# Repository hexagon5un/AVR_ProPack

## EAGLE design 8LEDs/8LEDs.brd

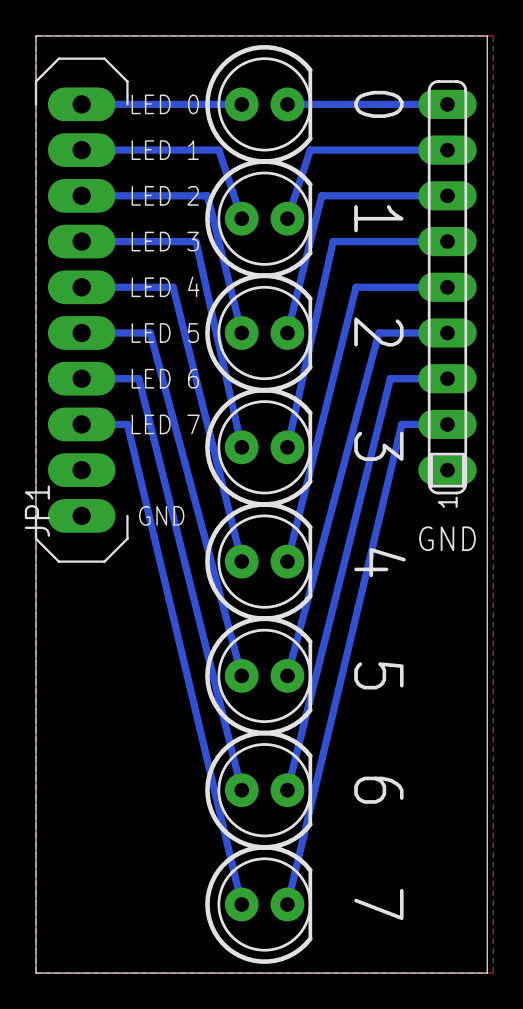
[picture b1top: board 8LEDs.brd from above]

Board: 2 copper layers, 25.1 x 52.1 mm, 10 parts (0 on the bottom side), 17 nets.

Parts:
JP1: M10"; 1X10LONGPAD
LED1, LED2, LED3, LED4, LED5, LED6, LED7, LED8: LED5MM
RN1: SIL9

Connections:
GND: JP1.1, RN1.1
unnamed: LED1.K, RN1.9
unnamed: LED2.K, RN1.8
unnamed: LED3.K, RN1.7
unnamed: LED4.K, RN1.6
unnamed: LED5.K, RN1.5
unnamed: LED6.K, RN1.4
unnamed: LED7.K, RN1.3
unnamed: LED8.K, RN1.2
unnamed: JP1.10, LED1.A
unnamed: JP1.9, LED2.A
unnamed: JP1.8, LED3.A
unnamed: JP1.7, LED4.A
unnamed: JP1.6, LED5.A
unnamed: JP1.5, LED6.A
unnamed: JP1.4, LED7.A
unnamed: JP1.3, LED8.A

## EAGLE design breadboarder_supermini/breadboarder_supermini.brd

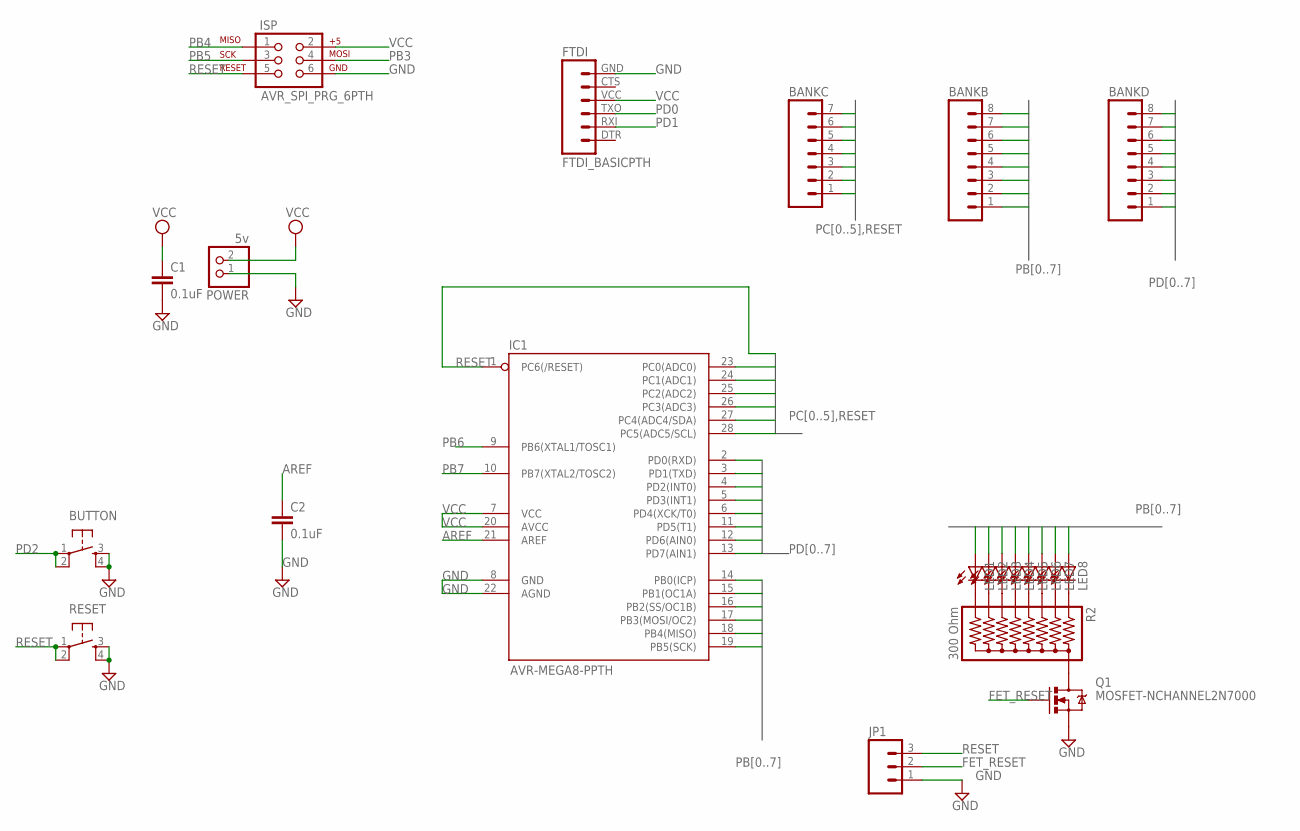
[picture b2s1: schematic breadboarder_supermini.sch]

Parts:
BANKB: M08LONGPADS; 1X08_LONGPADS
BANKC: M07LONGPADS; 1X07_LONGPADS
BANKD: M08LONGPADS; 1X08_LONGPADS
BUTTON: TAC_SWITCHPTH; TACTILE-PTH
C1, C2: 0.1uF; CAP-PTH-SMALL-KIT
FTDI: FTDI_BASICPTH; FTDI_BASIC
IC1: AVR-MEGA8-PPTH; DIL28-3
ISP: AVR_SPI_PRG_6PTH; 2X3
JP1: M03PTH; 1X03
LED1, LED2, LED3, LED4, LED5, LED6, LED7, LED8: LED3MM
POWER: 5v; 1X02
Q1: MOSFET-NCHANNEL2N7000; TO-92
R2: 300 Ohm; RPACK-SIP-PTH-8-LP
RESET: TAC_SWITCHPTH; TACTILE-PTH

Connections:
AREF: C2.1, IC1.21 (AREF)
FET_RESET: JP1.2, Q1.2 (G)
GND: BUTTON.3, BUTTON.4, C1.2, C2.2, FTDI.GND (6), IC1.8 (GND), IC1.22 (AGND), ISP.6, JP1.1, POWER.1, Q1.1 (S), RESET.3, RESET.4
unnamed: Q1.3 (D), R2.P$1 (1)
unnamed: LED1.K (C), R2.P$9 (9)
unnamed: LED2.K (C), R2.P$8 (8)
unnamed: LED3.K (C), R2.P$7 (7)
unnamed: LED4.K (C), R2.P$6 (6)
unnamed: LED5.K (C), R2.P$5 (5)
unnamed: LED6.K (C), R2.P$4 (4)
unnamed: LED7.K (C), R2.P$3 (3)
unnamed: LED8.K (C), R2.P$2 (2)
PB0: BANKB.8, IC1.14 (PB0(ICP)), LED1.A
PB1: BANKB.7, IC1.15 (PB1(OC1A)), LED2.A
PB2: BANKB.6, IC1.16 (PB2(SS/OC1B)), LED3.A
PB3: BANKB.5, IC1.17 (PB3(MOSI/OC2)), ISP.4, LED4.A
PB4: BANKB.4, IC1.18 (PB4(MISO)), ISP.1, LED5.A
PB5: BANKB.3, IC1.19 (PB5(SCK)), ISP.3, LED6.A
PB6: BANKB.2, IC1.9 (PB6(XTAL1/TOSC1)), LED7.A
PB7: BANKB.1, IC1.10 (PB7(XTAL2/TOSC2)), LED8.A
PC0: BANKC.7, IC1.23 (PC0(ADC0))
PC1: BANKC.6, IC1.24 (PC1(ADC1))
PC2: BANKC.5, IC1.25 (PC2(ADC2))
PC3: BANKC.4, IC1.26 (PC3(ADC3))
PC4: BANKC.3, IC1.27 (PC4(ADC4/SDA))
PC5: BANKC.2, IC1.28 (PC5(ADC5/SCL))
PD0: BANKD.8, FTDI.TXO (3), IC1.2 (PD0(RXD))
PD1: BANKD.7, FTDI.RXI (2), IC1.3 (PD1(TXD))
PD2: BANKD.6, BUTTON.1, BUTTON.2, IC1.4 (PD2(INT0))
PD3: BANKD.5, IC1.5 (PD3(INT1))
PD4: BANKD.4, IC1.6 (PD4(XCK/T0))
PD5: BANKD.3, IC1.11 (PD5(T1))
PD6: BANKD.2, IC1.12 (PD6(AIN0))
PD7: BANKD.1, IC1.13 (PD7(AIN1))
RESET: BANKC.1, IC1.1 (PC6(/RESET)), ISP.5, JP1.3, RESET.1, RESET.2
VCC: C1.1, FTDI.VCC (4), IC1.7 (VCC), IC1.20 (AVCC), ISP.2, POWER.2

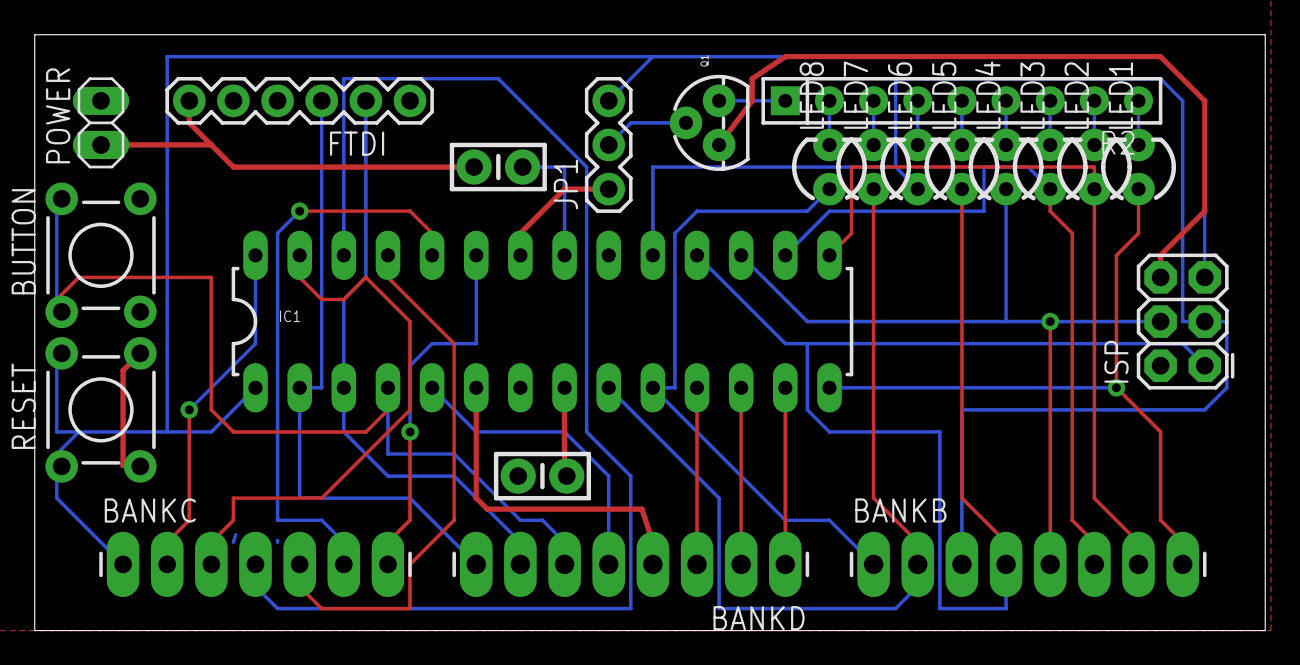
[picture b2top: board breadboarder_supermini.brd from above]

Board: 2 copper layers, 70.8 x 34.3 mm, 22 parts (0 on the bottom side), 36 nets.

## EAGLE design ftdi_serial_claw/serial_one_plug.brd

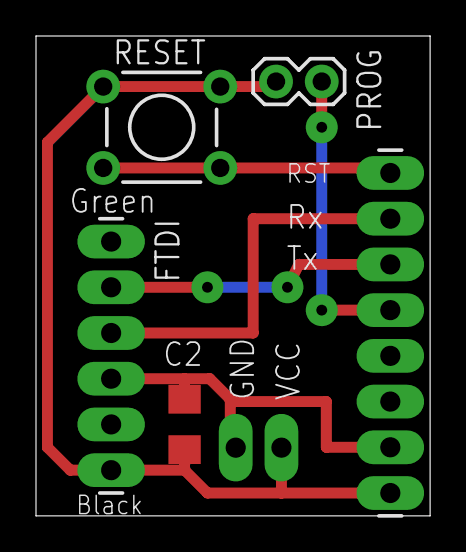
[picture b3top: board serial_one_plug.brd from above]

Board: 2 copper layers, 21.9 x 26.7 mm, 6 parts (0 on the bottom side), 6 nets.

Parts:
BOARD: 1X08_LONGPADS
C2: 0.1 uF; C1206
FTDI: 1X06_LONGPADS
POWER_RAIL: M02PTH3; 1X02_LONGPADS
PROG: M02PTH; 1X02
RESET: TACTILE-PTH

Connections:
GND: BOARD.1, C2.2, FTDI.6, POWER_RAIL.1, PROG.1, RESET.1, RESET.2
PD2: BOARD.5, PROG.2
RESET: BOARD.8, RESET.3, RESET.4
RX: BOARD.6, FTDI.2
TX: BOARD.7, FTDI.3
VCC: BOARD.2, C2.1, FTDI.4, POWER_RAIL.2

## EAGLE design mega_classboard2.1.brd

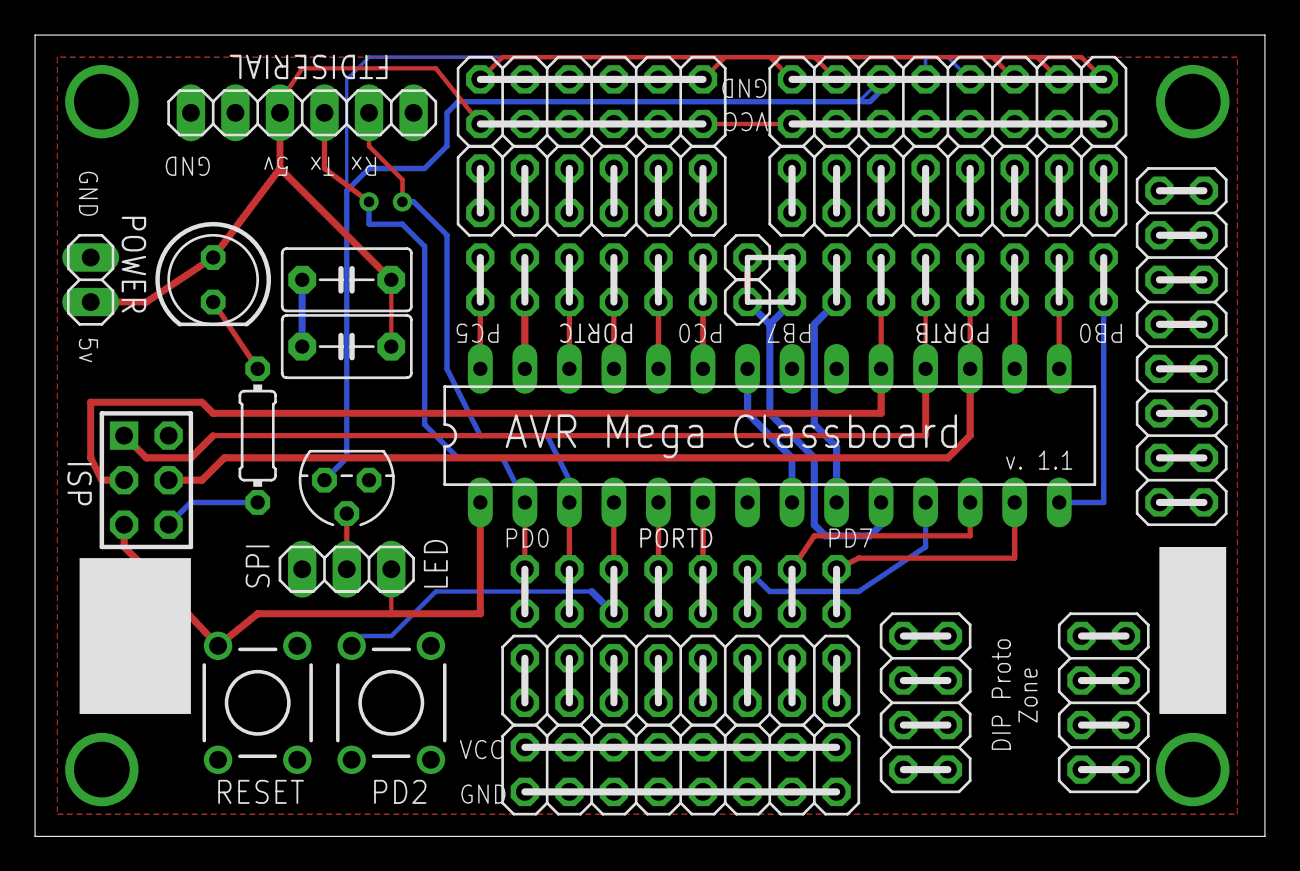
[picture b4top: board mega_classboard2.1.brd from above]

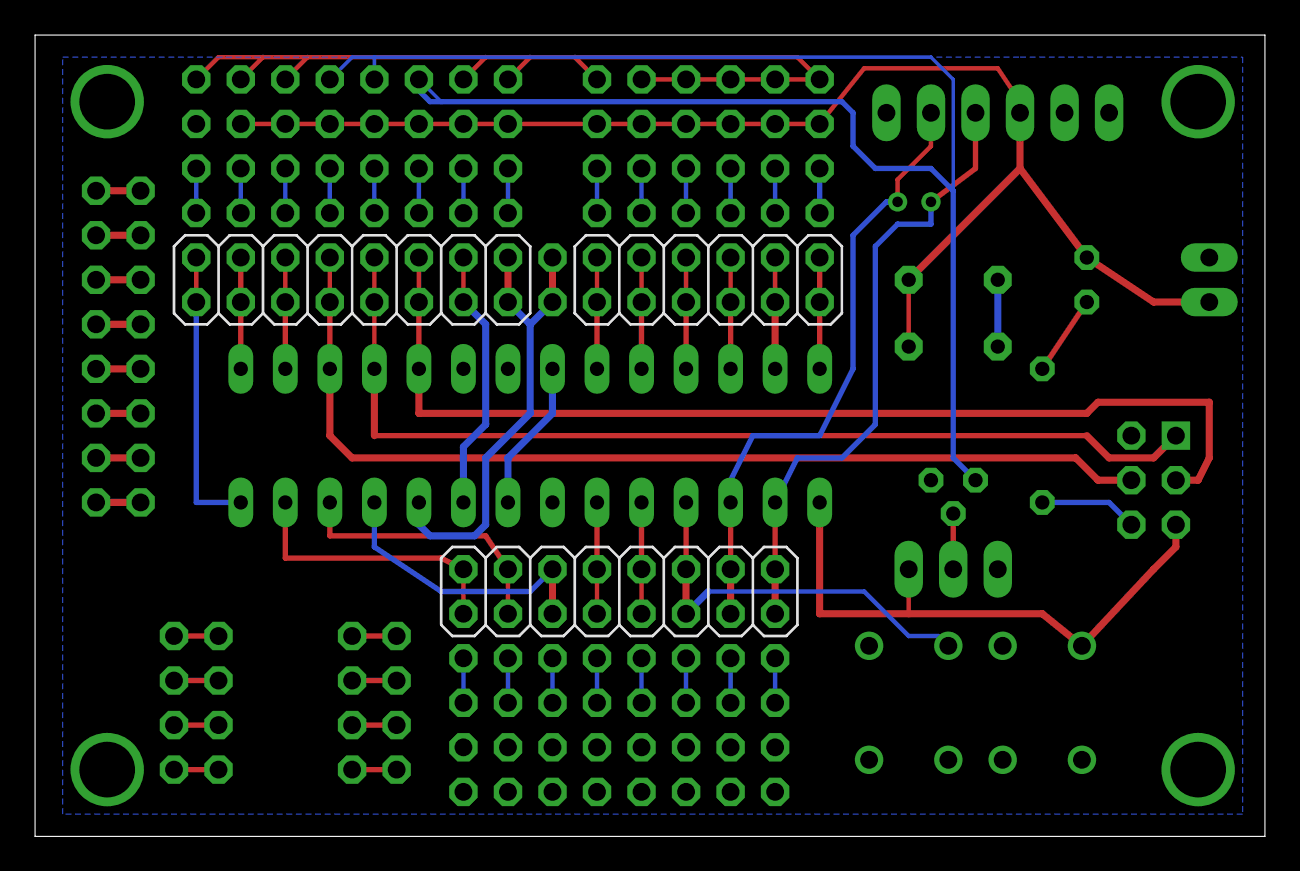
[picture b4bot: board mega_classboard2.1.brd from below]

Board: 2 copper layers, 70.2 x 45.7 mm, 30 parts (3 on the bottom side), 66 nets.

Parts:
A: SWITCH-MOMENTARY-2PTH; TACTILE-PTH
B: SWITCH-MOMENTARY-2PTH; TACTILE-PTH
BUFFER: 1u; C5B3.5
BUFFER1: 0.1u; C5B3.5
FTDISERIAL: 1X06
H1, H2, H3, H4: SPECIAL_DRILL_0.1250; PAD_0.1250
IC1: MEGA8-P; DIL28-3
ISP: AVR-ISP-6
JP1, JP2: 2X04
JP3, JP4, JP5, JP8, JP9: 2X08
JP6, JP10: 2X06
JP11, JP12: 1X01
PORTB: 2X08
PORTC: 2X06
PORTD: 2X08
POWER: 1X02
POWERLED: LED5MM
Q1: 2N7000; TO-92
R1: 200; 0204/7
SWITCHABLEGND: 1X03

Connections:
GND: A.1, B.1, BUFFER.2, BUFFER1.2, FTDISERIAL.1, IC1.8, IC1.22, ISP.6, JP8.1, JP8.3, JP8.5, JP8.13, JP8.15, JP9.1, JP9.3, JP9.5, JP9.7, JP9.9, JP9.11, JP9.13, JP9.15, JP10.1, JP10.3, JP10.5, JP10.7, JP10.9, JP10.11, POWER.2, Q1.1, R1.1, SWITCHABLEGND.3
unnamed: POWERLED.K, R1.2
unnamed: Q1.2, SWITCHABLEGND.2
unnamed: JP6.11, JP6.12
unnamed: JP6.9, JP6.10
unnamed: JP6.7, JP6.8
unnamed: JP6.5, JP6.6
unnamed: JP6.3, JP6.4
unnamed: JP6.1, JP6.2
unnamed: JP3.15, JP3.16
unnamed: JP3.13, JP3.14
unnamed: JP3.11, JP3.12
unnamed: JP3.9, JP3.10
unnamed: JP3.7, JP3.8
unnamed: JP3.5, JP3.6
unnamed: JP3.3, JP3.4
unnamed: JP3.1, JP3.2
unnamed: JP4.15, JP4.16
unnamed: JP4.13, JP4.14
unnamed: JP4.11, JP4.12
unnamed: JP4.9, JP4.10
unnamed: JP4.7, JP4.8
unnamed: JP4.5, JP4.6
unnamed: JP4.3, JP4.4
unnamed: JP4.1, JP4.2
unnamed: JP1.1, JP1.2
unnamed: JP1.3, JP1.4
unnamed: JP1.5, JP1.6
unnamed: JP1.7, JP1.8
unnamed: JP2.1, JP2.2
unnamed: JP2.3, JP2.4
unnamed: JP2.5, JP2.6
unnamed: JP2.7, JP2.8
unnamed: JP5.1, JP5.2
unnamed: JP5.3, JP5.4
unnamed: JP5.5, JP5.6
unnamed: JP5.7, JP5.8
unnamed: JP5.9, JP5.10
unnamed: JP5.11, JP5.12
unnamed: JP5.13, JP5.14
unnamed: JP5.15, JP5.16
unnamed: JP8.7, JP8.9, JP8.11, Q1.3
unnamed: A.3, IC1.1, ISP.5, SWITCHABLEGND.1
PORTB0: IC1.14, PORTB.1, PORTB.2
PORTB1: IC1.15, PORTB.3, PORTB.4
PORTB2: IC1.16, PORTB.5, PORTB.6
PORTB3: IC1.17, ISP.4, PORTB.7, PORTB.8
PORTB4: IC1.18, ISP.1, PORTB.9, PORTB.10
PORTB5: IC1.19, ISP.3, PORTB.11, PORTB.12
PORTB6: IC1.9, PORTB.13, PORTB.14
PORTB7: IC1.10, JP11.1, JP12.1, PORTB.15, PORTB.16
PORTC0: IC1.23, PORTC.1, PORTC.2
PORTC1: IC1.24, PORTC.3, PORTC.4
PORTC2: IC1.25, PORTC.5, PORTC.6
PORTC3: IC1.26, PORTC.7, PORTC.8
PORTC4: IC1.27, PORTC.9, PORTC.10
PORTC5: IC1.28, PORTC.11, PORTC.12
PORTD0: FTDISERIAL.4, IC1.2, PORTD.1, PORTD.2
PORTD1: FTDISERIAL.5, IC1.3, PORTD.3, PORTD.4
PORTD2: B.3, IC1.4, PORTD.5, PORTD.6
PORTD3: IC1.5, PORTD.7, PORTD.8
PORTD4: IC1.6, PORTD.9, PORTD.10
PORTD5: IC1.11, PORTD.11, PORTD.12
PORTD6: IC1.12, PORTD.13, PORTD.14
PORTD7: IC1.13, PORTD.15, PORTD.16
VCC: BUFFER.1, BUFFER1.1, FTDISERIAL.3, IC1.7, IC1.20, ISP.2, JP8.2, JP8.4, JP8.6, JP8.8, JP8.10, JP8.12, JP8.14, JP8.16, JP9.2, JP9.4, JP9.6, JP9.8, JP9.10, JP9.12, JP9.14, JP9.16, JP10.2, JP10.4, JP10.6, JP10.8, JP10.10, JP10.12, POWER.1, POWERLED.A

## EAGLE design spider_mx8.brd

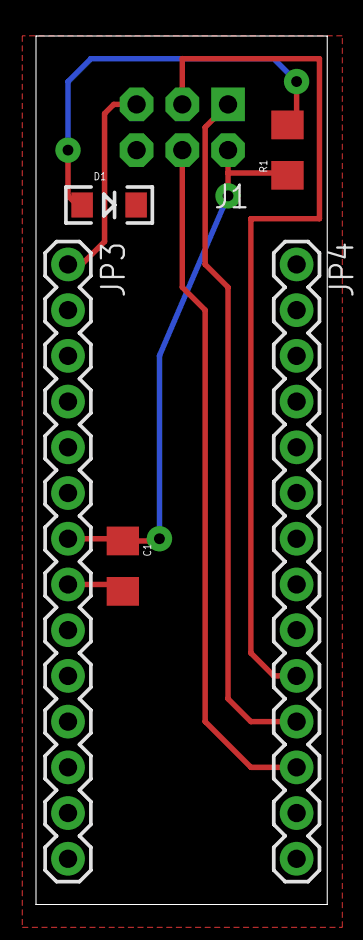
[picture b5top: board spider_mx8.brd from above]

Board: 2 copper layers, 16.2 x 48.2 mm, 6 parts (0 on the bottom side), 7 nets.

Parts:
C1: 0.1uF; 1206
D1: Yellow; LED-1206
J1: AVR_SPI_PRG_6NS; 2X3-NS
JP3, JP4: M14; 1X14
R1: 1k Ohm; 1206

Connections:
GND: C1.2, D1.C, J1.6, JP3.8
MISO: J1.1, JP4.11
MOSI: J1.4, JP4.12
unnamed: D1.A, R1.2
RESET: J1.5, JP3.1
SCK: J1.3, JP4.10
VCC: C1.1, J1.2, JP3.7, R1.1

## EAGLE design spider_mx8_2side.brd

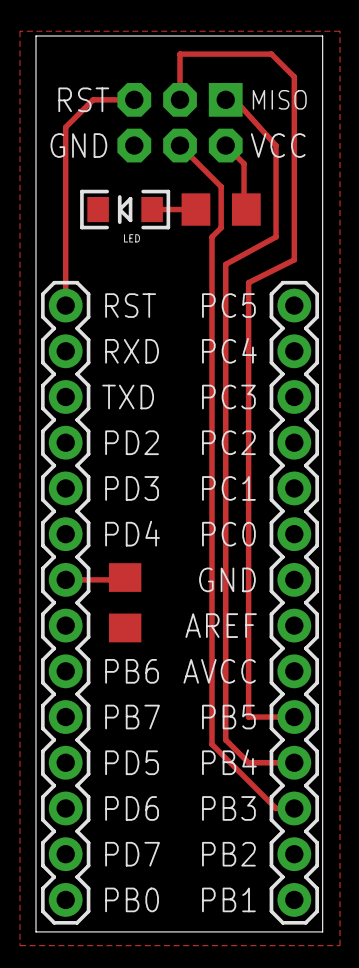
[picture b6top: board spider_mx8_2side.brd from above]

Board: 2 copper layers, 15.9 x 49.8 mm, 6 parts (0 on the bottom side), 7 nets.

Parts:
C1: 0.1uF; 1206
J1: AVR_SPI_PRG_6NS; 2X3-NS
JP1, JP3: M14; 1X14
LED: Yellow; LED-1206
R1: 1k Ohm; 1206

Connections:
GND: C1.2, J1.6, JP1.7, LED.C
MISO: J1.1, JP3.11
MOSI: J1.4, JP3.12
unnamed: LED.A, R1.2
RESET: J1.5, JP1.14
SCK: J1.3, JP3.10
VCC: C1.1, J1.2, JP1.8, R1.1

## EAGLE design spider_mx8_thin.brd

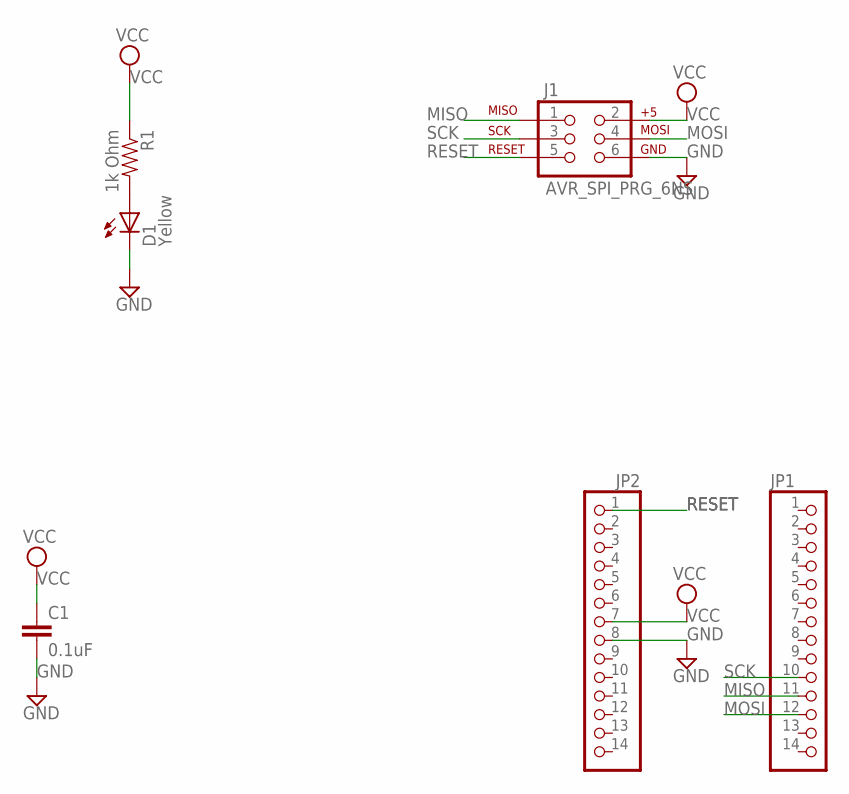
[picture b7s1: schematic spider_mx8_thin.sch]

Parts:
C1: 0.1uF; 1206
D1: Yellow; LED-1206
J1: AVR_SPI_PRG_6NS; 2X3-NS
JP1, JP2: PINHD-1X14; 1X14
R1: 1k Ohm; 1206

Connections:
GND: C1.2, D1.C, J1.6, JP2.8
MISO: J1.1, JP1.11
MOSI: J1.4, JP1.12
unnamed: D1.A, R1.2
RESET: J1.5, JP2.1
SCK: J1.3, JP1.10
VCC: C1.1, J1.2, JP2.7, R1.1

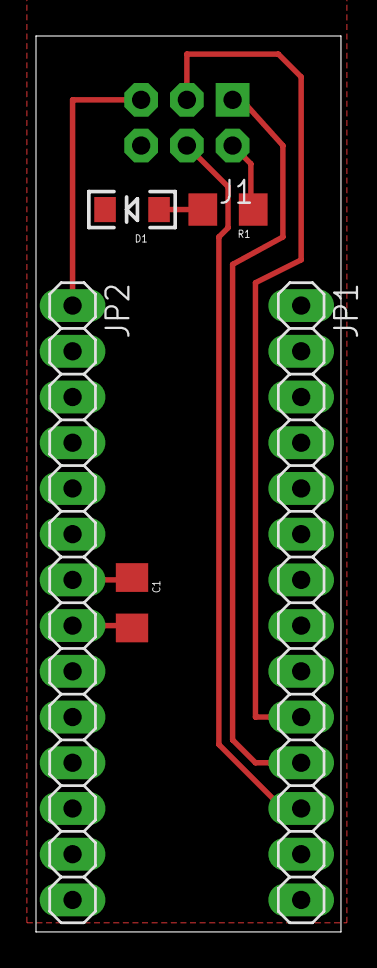
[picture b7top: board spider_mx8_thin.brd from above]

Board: 2 copper layers, 16.9 x 49.8 mm, 6 parts (0 on the bottom side), 7 nets.

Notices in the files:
parts and their libraries:
SparkFun-LED: Licensing: CC v3.0 Share-Alike You are welcome to use this library for commercial purposes.
